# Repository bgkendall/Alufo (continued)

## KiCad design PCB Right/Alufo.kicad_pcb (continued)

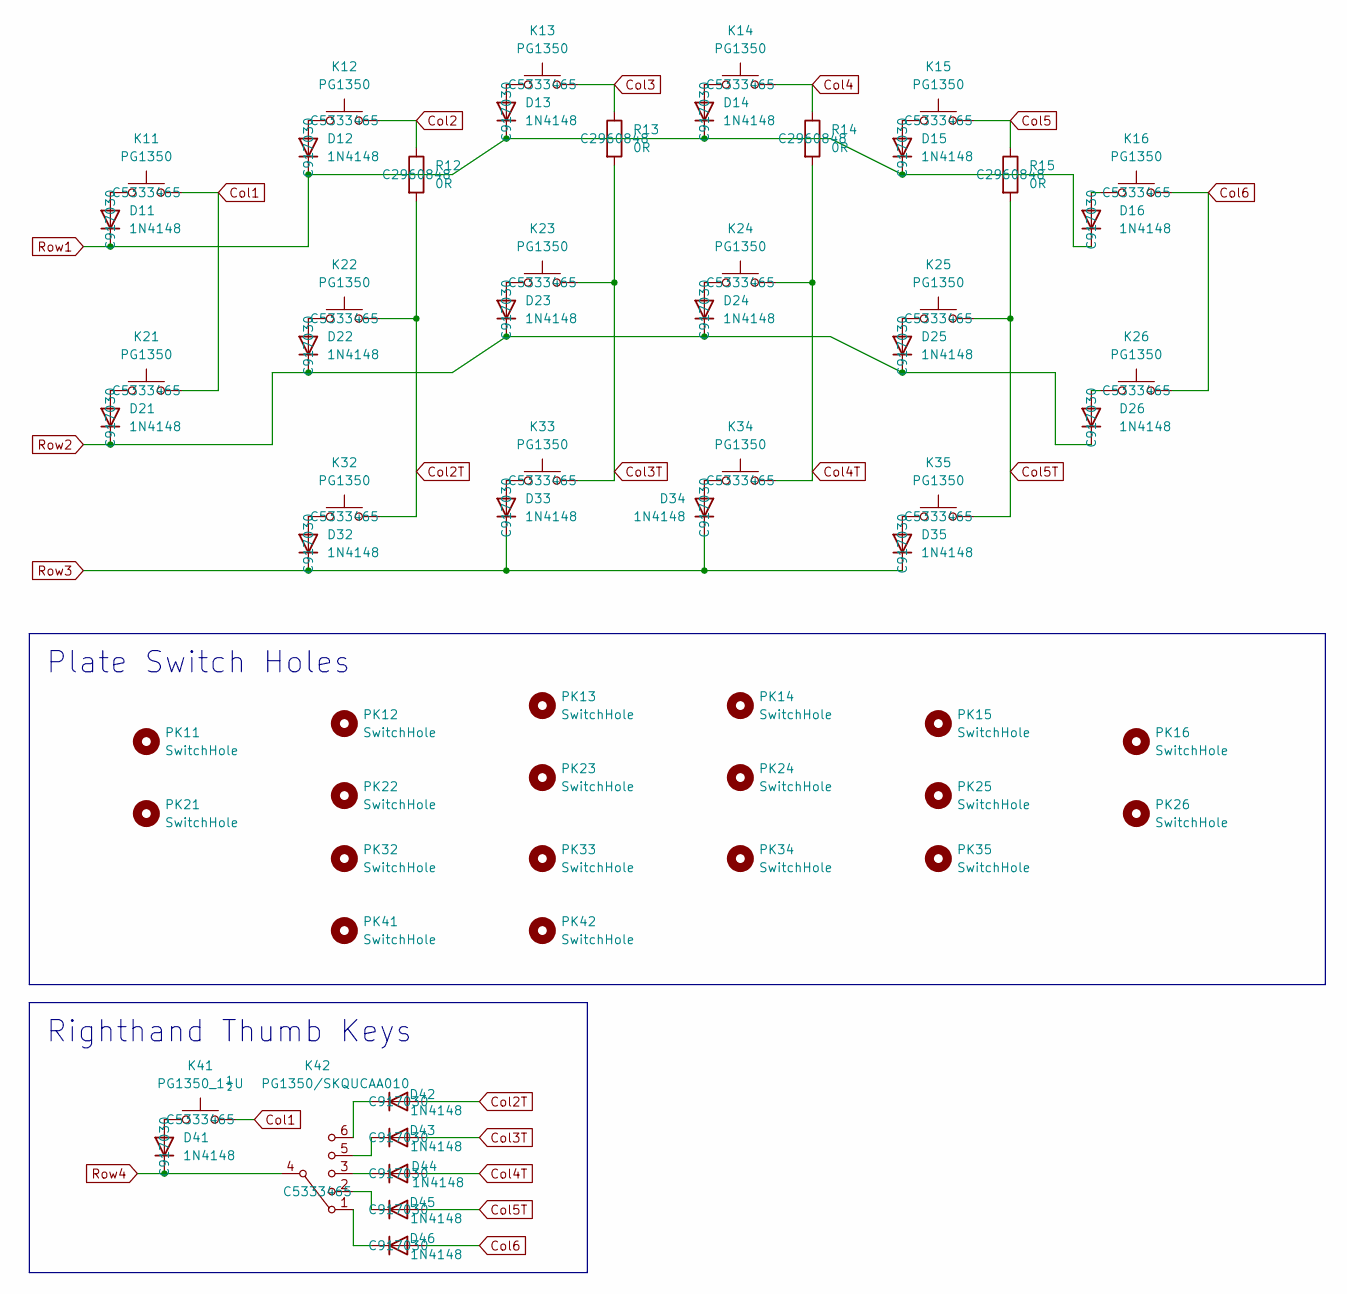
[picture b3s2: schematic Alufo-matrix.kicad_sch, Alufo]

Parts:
D11, D12, D13, D14, D15, D16, D21, D22, D23, D24, D25, D26, D32, D33, D34, D35: 1N4148; D_SOD-123_Mod; LCSC C917030
D41, D42, D43, D44, D45, D46: 1N4148; D_SOD-123; LCSC C917030
K11, K12, K13, K14, K15, K16, K21, K22, K23, K24, K25, K26, K32, K33, K34, K35: PG1350; SW_choc_v1_HS_CPG135001S30_1layer_1u; LCSC C5333465
K41: PG1350_1½U; SW_choc_v1_HS_CPG135001S30_1layer_1.5u; LCSC C5333465
K42: PG1350/SKQUCAA010; SW_choc_v1_HS_nav_CPG135001S30_SKQUCAA010_1layer_1u_1; LCSC C5333465
PK11, PK12, PK13, PK14, PK15, PK16, PK21, PK22, PK23, PK24, PK25, PK26, PK32, PK33, PK34, PK35, PK42: SwitchHole; SW_choc_v1_Plate_CPG135001S30_1u
PK41: SwitchHole; SW_choc_v1_Plate_CPG135001S30_1.5u
R12, R13, R14, R15: 0R; R_2010_5025Metric; LCSC C2960848

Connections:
Col1: K11.1, K21.1, K41.1; also elsewhere on the board
Col2: K12.1, R12.1; also elsewhere on the board
Col2T: D42.2 (A), K22.1, K32.1, R12.2
Col3: K13.1, R13.1; also elsewhere on the board
Col3T: D43.2 (A), K23.1, K33.1, R13.2
Col4: K14.1, R14.1; also elsewhere on the board
Col4T: D44.2 (A), K24.1, K34.1, R14.2
Col5: K15.1, R15.1; also elsewhere on the board
Col5T: D45.2 (A), K25.1, K35.1, R15.2
Col6: D46.2 (A), K16.1, K26.1; also elsewhere on the board
unnamed: D11.2 (A), K11.2
unnamed: D12.2 (A), K12.2
unnamed: D13.2 (A), K13.2
unnamed: D14.2 (A), K14.2
unnamed: D15.2 (A), K15.2
unnamed: D16.2 (A), K16.2
unnamed: D21.2 (A), K21.2
unnamed: D22.2 (A), K22.2
unnamed: D23.2 (A), K23.2
unnamed: D24.2 (A), K24.2
unnamed: D25.2 (A), K25.2
unnamed: D26.2 (A), K26.2
unnamed: D32.2 (A), K32.2
unnamed: D33.2 (A), K33.2
unnamed: D34.2 (A), K34.2
unnamed: D35.2 (A), K35.2
unnamed: D41.2 (A), K41.2
unnamed: D42.1 (K), K42.6 (Ctr)
unnamed: D43.1 (K), K42.5 (D)
unnamed: D44.1 (K), K42.3 (C)
unnamed: D45.1 (K), K42.2 (B)
unnamed: D46.1 (K), K42.1 (A)
Row1: D11.1 (K), D12.1 (K), D13.1 (K), D14.1 (K), D15.1 (K), D16.1 (K); also elsewhere on the board
Row2: D21.1 (K), D22.1 (K), D23.1 (K), D24.1 (K), D25.1 (K), D26.1 (K); also elsewhere on the board
Row3: D32.1 (K), D33.1 (K), D34.1 (K), D35.1 (K); also elsewhere on the board
Row4: D41.1 (K), K42.4 (Com); also elsewhere on the board

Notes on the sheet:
Plate Switch Holes
Righthand Thumb Keys

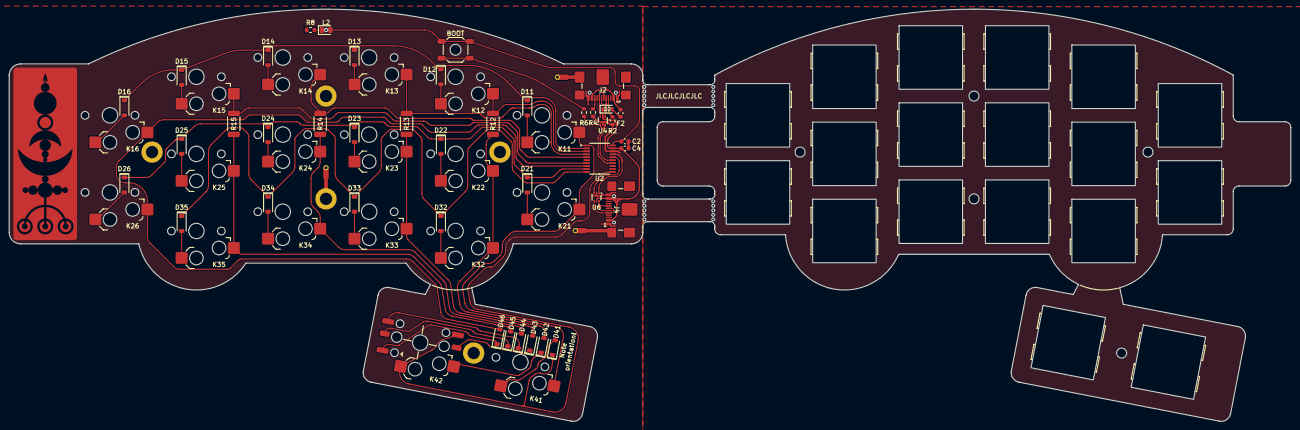
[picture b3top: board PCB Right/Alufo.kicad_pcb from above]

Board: 2 copper layers, 282.6 x 90.9 mm, 94 parts (0 on the bottom side), 56 nets.

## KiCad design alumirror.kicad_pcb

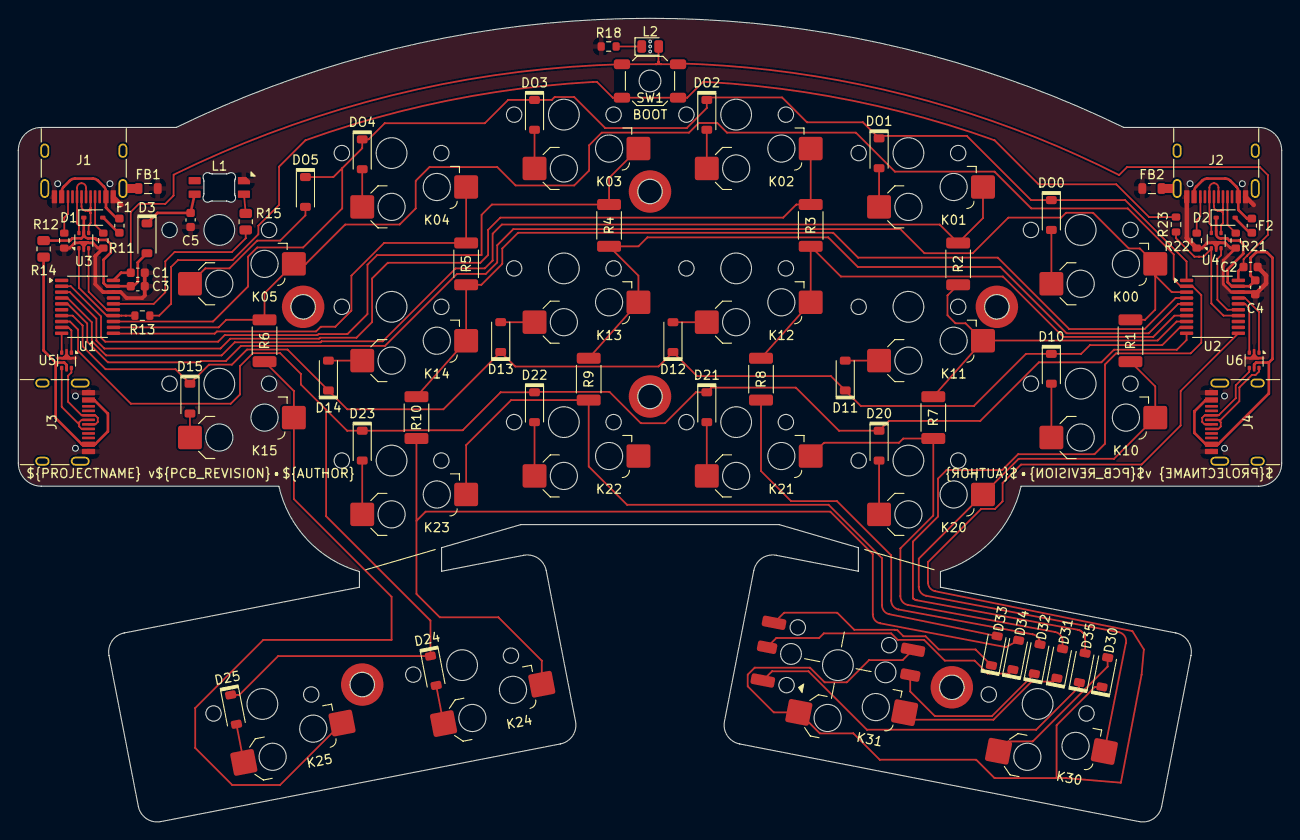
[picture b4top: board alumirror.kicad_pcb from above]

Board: 2 copper layers, 139.7 x 88.9 mm, 96 parts (0 on the bottom side), 82 nets.

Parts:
C1, C2, C3, C4, C5: 100nF; C_0603_1608Metric
D1, D2: PMEG2010EA; D_SOD-323
D3, D30, D31, D32, D33, D34, D35: 1N4148; D_SOD-123
D10, D11, D12, D13, D14, D15, D20, D21, D22, D23, D24, D25: 1N4148; D_SOD-123_Mod
DO0, DO1, DO2, DO3, DO4, DO5: 1N4148; D_SOD-123_Mod
F1, F2: 500mA; Fuse_0603_1608Metric
FB1, FB2: FerriteBead; L_0805_2012Metric
H1, H2, H3, H4, H5, H6: MountingHole; MountingHole_2.2mm_M2_SMD_Solder_Nut
J1, J2, J3, J4: USB_C_Receptacle_USB2.0_16P_2SH; USB_C_Receptacle_HRO_TYPE-C-31-M-12
K00, K01, K02, K03, K04, K05, K10, K11, K12, K13, K14, K15, K20, K21, K22, K23, K24: PG1350; SW_choc_v1_HS_CPG135001S30_1layer_1u
K25, K30: PG1350_1½U; SW_choc_v1_HS_CPG135001S30_1layer_1.5u
K31: PG1350/SKQUCAA010; SW_choc_v1_HS_nav_CPG135001S30_SKQUCAA010_1layer_1u_1
L1: SK6812MINI-E; LED_6028R
L2: LED; LED_0805_2012Metric_Mod
NT1, NT2: NetTie_2; NetTie-2_SMD_Pad0.2mm
R1, R2, R3, R4, R5, R6, R7, R8, R9, R10: 0R; R_2010_5025Metric_Mod
R11, R12, R21, R22: 5k1; R_0603_1608Metric
R13, R18, R23: 10k; R_0603_1608Metric
R14: 0R; R_0805_2012Metric
R15: 470R; R_0805_2012Metric
SW1: BOOT; SW_SPST_SKQG_WithStem
U1, U2: CH552T; TSSOP-20_4.4x6.5mm_P0.65mm
U3, U4, U5, U6: USBLC6-2P6; SOT-666_Mod

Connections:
+3V3: C1.1, C2.1, L2.2 (A), SW1.2, U1.20 (V33), U2.20 (V33)
BOOT: R13.2, R23.2, SW1.1
Col0: K00.1, R1.1, U1.5 (P1.7), U2.3 (P1.5)
Col0T: K10.1, K20.1, K30.1, R1.2
Col1L: K01.1, R2.1, U1.4 (P1.6)
Col1R: K11.1, R2.2, R7.1, U2.8 (P1.1)
Col1RT: D31.2 (A), K21.1, R7.2
Col2L: K02.1, R3.1, U1.3 (P1.5)
Col2R: K12.1, R3.2, R8.1, U2.7 (P1.0)
Col2RT: D32.2 (A), K22.1, R8.2
Col3L: K03.1, R4.1, U1.2 (P1.4)
Col3R: K13.1, R4.2, R9.1, U2.5 (P1.7)
Col3RT: D33.2 (A), K23.1, R9.2
Col4L: K04.1, R5.1, U1.11 (P3.3)
Col4R: K14.1, R5.2, R10.1, U2.4 (P1.6)
Col4T: D34.2 (A), K24.1, R10.2
Col5: D35.2 (A), K05.1, R6.1, U1.12 (P3.4), U2.2 (P1.4)
Col5T: K15.1, K25.1, R6.2
GND: C1.2, C2.2, C3.2, C4.2, C5.2, FB1.2, FB2.2, J1.A1 (GND), J1.A12 (GND), J1.B1 (GND), J1.B12 (GND), J2.A1 (GND), J2.A12 (GND), J2.B1 (GND), J2.B12 (GND), J3.A1 (GND), J3.A12 (GND), J3.B1 (GND), J3.B12 (GND), J4.A1 (GND), J4.A12 (GND), J4.B1 (GND), J4.B12 (GND), L1.4 (VSS), R11.2, R12.2, R18.2, R21.2, R22.2, U1.18 (GND), U2.18 (GND), U3.2 (GND), U4.2 (GND), U5.2 (GND), U6.2 (GND)
LED: R15.1, U1.16 (P1.3)
unnamed: D1.2 (A), F1.2
unnamed: D2.2 (A), F2.2
unnamed: C5.1, D3.1 (K), L1.1 (VDD)
unnamed: D10.2 (A), K10.2
unnamed: D11.2 (A), K11.2
unnamed: D12.2 (A), K12.2
unnamed: D13.2 (A), K13.2
unnamed: D14.2 (A), K14.2
unnamed: D15.2 (A), K15.2
unnamed: D20.2 (A), K20.2
unnamed: D21.2 (A), K21.2
unnamed: D22.2 (A), K22.2
unnamed: D23.2 (A), K23.2
unnamed: D24.2 (A), K24.2
unnamed: D25.2 (A), K25.2
unnamed: D30.2 (A), K30.2
unnamed: D31.1 (K), K31.6 (Ctr)
unnamed: D32.1 (K), K31.5 (D)
unnamed: D33.1 (K), K31.3 (C)
unnamed: D34.1 (K), K31.2 (B)
unnamed: D35.1 (K), K31.1 (A)
unnamed: DO0.2 (A), K00.2
unnamed: DO1.2 (A), K01.2
unnamed: DO2.2 (A), K02.2
unnamed: DO3.2 (A), K03.2
unnamed: DO4.2 (A), K04.2
unnamed: DO5.2 (A), K05.2
unnamed: FB1.1, J1.S2 (SHIELD)
unnamed: FB2.1, J2.S1 (SHIELD)
unnamed: J1.A5 (CC1), R11.1
unnamed: J1.B5 (CC2), R12.1
unnamed: J2.A5 (CC1), R21.1
unnamed: J2.B5 (CC2), R22.1
unnamed: L1.3 (DIN), R15.2
unnamed: L2.1 (K), R18.1
unnamed: NT1.2, R13.1
unnamed: NT2.2, R23.1
RX_L: U1.10 (P3.0), U5.3 (I/O2)
RX_PL: J3.A6 (D+), J3.B6 (D+), U5.4 (I/O2)
RX_PR: J4.A7 (D-), J4.B7 (D-), U6.6 (I/O1)
RX_R: U2.17 (P1.2), U6.1 (I/O1)
Row0: DO0.1 (K), DO1.1 (K), DO2.1 (K), DO3.1 (K), DO4.1 (K), DO5.1 (K), U1.13 (P3.5), U2.1 (P3.2)
Row1: D10.1 (K), D11.1 (K), D12.1 (K), D13.1 (K), D14.1 (K), D15.1 (K), U1.7 (P1.0), U2.9 (P3.1)
Row2: D20.1 (K), D21.1 (K), D22.1 (K), D23.1 (K), D24.1 (K), D25.1 (K), U1.8 (P1.1), U2.10 (P3.0)
Row3R: D30.1 (K), K31.4 (Com), U2.11 (P3.3)
TX_L: U1.9 (P3.1), U5.1 (I/O1)
TX_PL: J3.A7 (D-), J3.B7 (D-), U5.6 (I/O1)
TX_PR: J4.A6 (D+), J4.B6 (D+), U6.4 (I/O2)
TX_R: U2.16 (P1.3), U6.3 (I/O2)
USB_L+: NT1.1, U1.14 (P3.6/UDP), U3.1 (I/O1)
USB_L-: U1.15 (P3.7/UDM), U3.3 (I/O2)
USB_PL+: J1.A6 (D+), J1.B6 (D+), U3.6 (I/O1)
USB_PL-: J1.A7 (D-), J1.B7 (D-), U3.4 (I/O2)
USB_PR+: J2.A6 (D+), J2.B6 (D+), U4.6 (I/O1)
USB_PR-: J2.A7 (D-), J2.B7 (D-), U4.4 (I/O2)
USB_R+: NT2.1, U2.14 (P3.6/UDP), U4.1 (I/O1)
USB_R-: U2.15 (P3.7/UDM), U4.3 (I/O2)
VBUS_L: F1.1, J1.A4 (VBUS), J1.A9 (VBUS), J1.B4 (VBUS), J1.B9 (VBUS)
VBUS_R: F2.1, J2.A4 (VBUS), J2.A9 (VBUS), J2.B4 (VBUS), J2.B9 (VBUS)
VCC_L: C3.1, D1.1 (K), D3.2 (A), R14.1, U1.19 (VCC), U3.5 (VBUS)
VCC_L': J3.A4 (VBUS), J3.A9 (VBUS), J3.B4 (VBUS), J3.B9 (VBUS), R14.2, U5.5 (VBUS)
VCC_R: C4.1, D2.1 (K), J4.A4 (VBUS), J4.A9 (VBUS), J4.B4 (VBUS), J4.B9 (VBUS), U2.19 (VCC), U4.5 (VBUS), U6.5 (VBUS)

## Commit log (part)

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2024-07-17 Add license.
2024-07-21 Add initial version
    Very rough routing of matrix
    No USB ports, etc.
2024-07-21 Add 3D model pocket areas for all matrix components
    User 1–4 layers of switches, diodes and resistors now contain areas that will be excluded from the 3D print for the bottom-mid case. This will allow space for these components. These areas are constr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
2024-07-22 Tweak edge cuts
    Also add keycap outlines to back silkscreen so they can be seen when viewing the 3D board model.
2024-07-22 Re-work thumb key connections
    The lefthand thumb keys are now on row 2, columns 0 and 5. This frees up a pin for potential red, green *and blue* LEDs.
    The righthand thumb keys remain on their own row. This is easier to route and allows for a 5-way navigation switch to be added.
2024-07-27 Add 3D model for SKQUAAA010
    The board actually uses a SKQUCAA010, but this is close enough
    Model from https://www.snapeda.com/parts/SKQUAAA010/ALPS/view-part/
2024-07-27 Create combined choc/nav. switch footprint and use for SW31
2024-07-27 Add missing middle case layer cutout section for switches
2024-07-27 Remove SKQUAAA010 3D model
2024-07-27 Move bottom row one column over
    This allows the left thumb keys to be on adjacent columns and saves routing Column 0 all the way across the board.
2024-07-27 Tidy routing
2024-07-28 Add lefthand USB, ESD, etc. components to schematic
2024-07-28 Renamed all key switches to K##
2024-07-29 Add LEDs
2024-07-30 Add 0603 LED footprint with holes and 3D model cutouts
    The drill holes will allow the LED to be visible through the PCB that will act as the base.
2024-07-30 Add 3D model cutout to SKQG switch footprint
    More than just the boot hole pass-through!
2024-07-30 Tweak silkscreen of combined choc/nav switch footprint
2024-07-31 Add righthand active components
    Routing is **very** rough
2024-07-31 Relocate lefthand capacitors
2024-07-31 Rearrange components for better layout
2024-08-02 Convert 3D model cutout outlines to polygons
    This gives more flexibility to the shapes and is less clutter on the board.
2024-08-04 Add custom SOT-666 footprint
    Footprint has ground routing and 3D cutout
2024-08-04 Fix USBLC6’s silkscreen locations
2024-08-06 Rotate thumb keys and set outline
    Thumb keys rotated by 11° and lined up
    Margin around thumb keys is ⅛ vertical U (2.125mm)
2024-08-06 Add footprint for solder nuts
    3.5mm high M2 solder nuts will be used between the PCB that will act as the base of the board and the active PCB. They will not be soldered with any other components.
2024-08-06 Add mounting holes and re-route tracks around them
2024-08-08 Change RGB LED decoupling capacitor (C5)
    Use 100nF — there seems to be some contradictory information on this, but this seems to be the consensus.
    Use 0603 size since the capacitance now matches C1–4, which are this size.
2024-08-10 Adjust component locations
2024-08-10 Add logo
2024-08-10 Change project name to Title Case
2024-08-11 Clean up edges around thumb keys
2024-08-11 Switch R14 back to 2010 size
2024-08-12 Renumber components
    * For single-digit components:
    * Odd numbers are populated on the lefthand board only
    * Even numbers are populated on the righthand board only
    * Double-digit components are populated on both sides
2024-08-12 Update resistor values
    Testing seemed to show that 5.1KΩ will work well for a dim power LED.
    The value for the boot resistor is not well defined, but values from 5.1KΩ to 20KΩ have been seem.
    (Using 5.1KΩ for these means that the same resistor stock used for USB power control can be used.)
2024-08-12 Start to clean up traces
2024-08-14 Remove ground fill from thumb areas
2024-08-16 Switch label to mask instead of silkscreen
2024-09-15 Switch K22 to new “clipped” footprint
    Clipped footprint has a cut-out in one of the hot-swap socket pads to avoid proximity warning with solder nut pad.
    Also tweaked and rounded multiple traces.
2024-09-23 Test left-hand only components, outline and routing
2024-09-23 Create righthand PCB
2024-09-23 Change thumb keys to columns 1 and 6
2024-09-23 Updated Row 3 diode placement
2024-09-26 Change project name from Alumirror to Alufo
    Since it is likely that the left and right hand PCBs will be split, there won’t actually be much mirroring going on (also most split keyboards are mirrored left to right, so that not particularly spe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
2024-09-26 Create separate projects for left and right hands
2024-09-26 Remove lefthand components from righthand board
2024-09-26 Clean-up left/righthand schematics
2024-09-26 Remove status LED resistor
2024-09-27 Realign columns on righthand side
2024-09-27 Route Row 2 under upper 0Ω resistors
    TODO: Reconnect Column 6 to thumb row
2024-09-27 Route Row 3 under upper 0Ω resistors and remove lower 0Ω resistors
2024-09-27 Tweak D26 location
2024-09-27 Route Row 2 under upper 0Ω resistors
2024-09-27 Route Row 3 under upper 0Ω resistors
2024-09-27 Remove “L” from column labels
2024-09-27 Renumber previously common components
2024-09-27 Add silkscreen to show board curve on thumb cluster connector
    (In case someone wanted to remove either or both of the thumb clusters.)
2024-09-28 Add lock files to Git ignored list
2024-09-30 Clean up routing through jumper resistors
2024-09-30 Align R16 with socket pads
2024-10-02 Clean up routing of right thumb keys
2024-10-20 Make NetTie narrower
2024-10-20 Clean-up traces on righthand board
    Also make tweaks to lefthand
2024-10-21 Further routing tweaks
2024-10-21 Power routing tweaks
2024-10-21 Fix boot access hole location
    Because the lefthand side PCB will become the base for the righthand board (and vice versa), and because the boot button is no longer centred, the hole in the base to allow access to the button must 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
2024-10-22 Update lefthand title block and dynamic text
2024-10-22 Revert boot access hole change
    It was correct before!
2024-10-22 Fix alignment of thumb cluster screw hole
    It did not line up when one side’s PCB was used as a base for the other.
2024-10-24 Add order number location
2024-10-26 Move thumb clusters down 2mm
2024-10-26 Add plate to righthand board
2024-11-01 Do not exclude solder nuts from BOM
2024-11-08 Rename PCB directories
2024-11-08 Move logo originals to Design folder
2024-11-08 Clip leftmost socket pad on thumb row
    The middle layer wall should now be ~1.5mm thick next to that pad instead of just ½mm.
2024-11-08 Expand cutout for boot switch to avoid slender wall
2024-11-08 Increase cutouts for solder nuts to avoid thin walls
    The cutouts now merge with adjacent switch cutouts rather than leaving a very thin gap.
    The solder nut that connects to the shield is a separate footprint that does not need to be expanded.
2024-11-08 Further increase size of solder nut cutout
    Decrease size of right thumb diode cutout to prevent a thin wall between it and the larger solder nut cutout.
2024-11-09 Add Gerber archives
2024-11-09 Set minimum hole size to 0.65mm
    This is the minimum hole size JLC can support on aluminium boards.
    The following changes were made:
    * Power LED now has a single 0.7mm hole instead of three 0.3mm ones. (This is for the light to shine through the PCB that will act as the base.)
    * Mouse-bite holes changed from 0.5mm to 0.65mm and moved accordingly.
    * USB port leg holes *and pads* now 0.05mm wider.
    Also smoothed out ground plane connection on ESD chips. (Now uses arcs instead of a trapezoid pad.)
2024-11-10 Update middle layer cutouts
    There was no need for separate heights for the diodes and switch legs as it turned out to be only 0.1mm difference between them.
    To apply this and take advantage of the default KiCad colours the following changes were made:
    * User.1 (2010 resistors) moved to User.2
    * User.2 (diodes) merged into User.3
    * User.6 (100% holes) moved to User.9
2024-11-10 Add middle layer model design
    The SVGs exported from KiCad have been included even though they are transient files.
2024-11-10 Add cutout in middle layer for solder jump
2024-12-11 Test direct wiring to an STM32 chip
    Sort of works, but there might not be enough room to route all the key connections while keeping good track separation. This would be even worse on the righthand side with the five-way switch!
2024-12-12 Add LCSC part numbers to left side
2024-12-14 Switch to STM32F042K6T6
2024-12-15 Unset DNP on all symbols
    It causes the symbol to be obscured by a big red cross in the schematic!
2024-12-15 Join up column 6 and remove shield jumper J5
    Reroute some tracks around the column 6 layer jump given more space than a 2010 resistor.
2024-12-15 Remove mid-layer cutouts for 0Ω resistors
2024-12-16 Add ground plane to back
2024-12-16 Apply similar changes to right PCB
2024-12-31 Moved MCU
    Still awful!
2024-12-31 Tie pins 19 and 20 to ground
    This solves the disconnected ground areas.
2025-01-05 Modify left PCB to use STM32C071F MCU
    Seems like it could work!
2025-04-01 Update project library name in schematic
2025-04-01 Update to KiCad v9
2025-04-01 Switch to SMD USB ports
2025-04-01 Update right side
    Also add outline for middle layer to new USB port footprint (although it won’t be right.
2025-04-03 Update version number in logo
2025-04-03 Add warning for nav. switch diode’s direction
    Also fixed these diode’s labels, which had reset to a bad location.
2025-04-08 Remove 0Ω resistor (R9) on VCC line
    Rework some routing around USB port.
    Remove keep out areas from switch to allow additional ground connections.
    Use personal SOD-323 footprint.
2025-04-08 Add additional pads to USB ports for strength
    Also apply tweaks from left PCB to right.
2025-04-10 Move righthand USB port in
    Moved port and associated components 19.05÷12mm left to account for SMD legs.
2025-04-10 Remove righthand R11
    Col1 now routed under MCU between K11 and K21 instead of through jumper.
    Row1 and Col1 pins on MCU swapped.
2025-04-10 Update LCSC part number for USB ports
    Also hide LCSC numbers erroneously showing in schematic.
2025-04-10 Update extra USB port solder pad
    The pad should now not overlap with parts of the port casing that have no metal.
2025-04-11 Add shield connectors
    The USB ports will now be connected to the aluminium PCB core. This is done using a 0.6mm diameter wire. One end of the wire will be soldered to a pad on the PCB and the other will pass through a hol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
    Also, R9, the 0Ω resistor on the lefthand VCC line has returned to allow a more direct ground route between the USB port and the MCU. However it is now a smaller 0805 size resistor.
2025-04-11 Add shield connection to H3 (lower middle mounting hole)
2025-04-11 Update middle layer cutouts for USB ports
    Also slightly increase length of USB port pads.
2025-04-12 Add FreeCAD Python script to generate middle layer
2025-04-12 Modularise middle layer generator
2025-04-13 Remove FreeCAD profect file
    It can be generated using the new script.
2025-04-13 Rename PCB project files
2025-04-13 Rename lefthand PCB project internally
2025-04-13 Add separate plate PCB
2025-04-13 Create export directory for middle layer
2025-04-13 Fix issues in Edge Cuts that cause FreeCAD to think outline is incomplete
2025-04-13 Add new STLs for middle layers
2025-04-14 Move cutout for lefthand MCU area to User.5
    This allows the cutout to be more easily changed than a polygon would. The middle layer generation script has been updated to accommodate this.
    Other changes to the script:
    * Logging is improved.
    * Layers are cut from the previous one immediately after generated. (Cutting in one go at the end proved to be unreliable — possibly timed out??)
2025-04-21 Tweak positioning of shield connections
    Should now be the same on each side and align with other elements.
